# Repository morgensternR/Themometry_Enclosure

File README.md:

# Themometry_Enclosure
Initial Motherboard design to organize thermometry

 Copyright 2023 Ryan Morgenstern

   Licensed under the Apache License, Version 2.0 (the "License");
   you may not use this file except in compliance with the License.
   You may obtain a copy of the License at

       http://www.apache.org/licenses/LICENSE-2.0

   Unless required by applicable law or agreed to in writing, software
   distributed under the License is distributed on an "AS IS" BASIS,
   WITHOUT WARRANTIES OR CONDITIONS OF ANY KIND, either express or implied.
   See the License for the specific language governing permissions and
   limitations under the License.

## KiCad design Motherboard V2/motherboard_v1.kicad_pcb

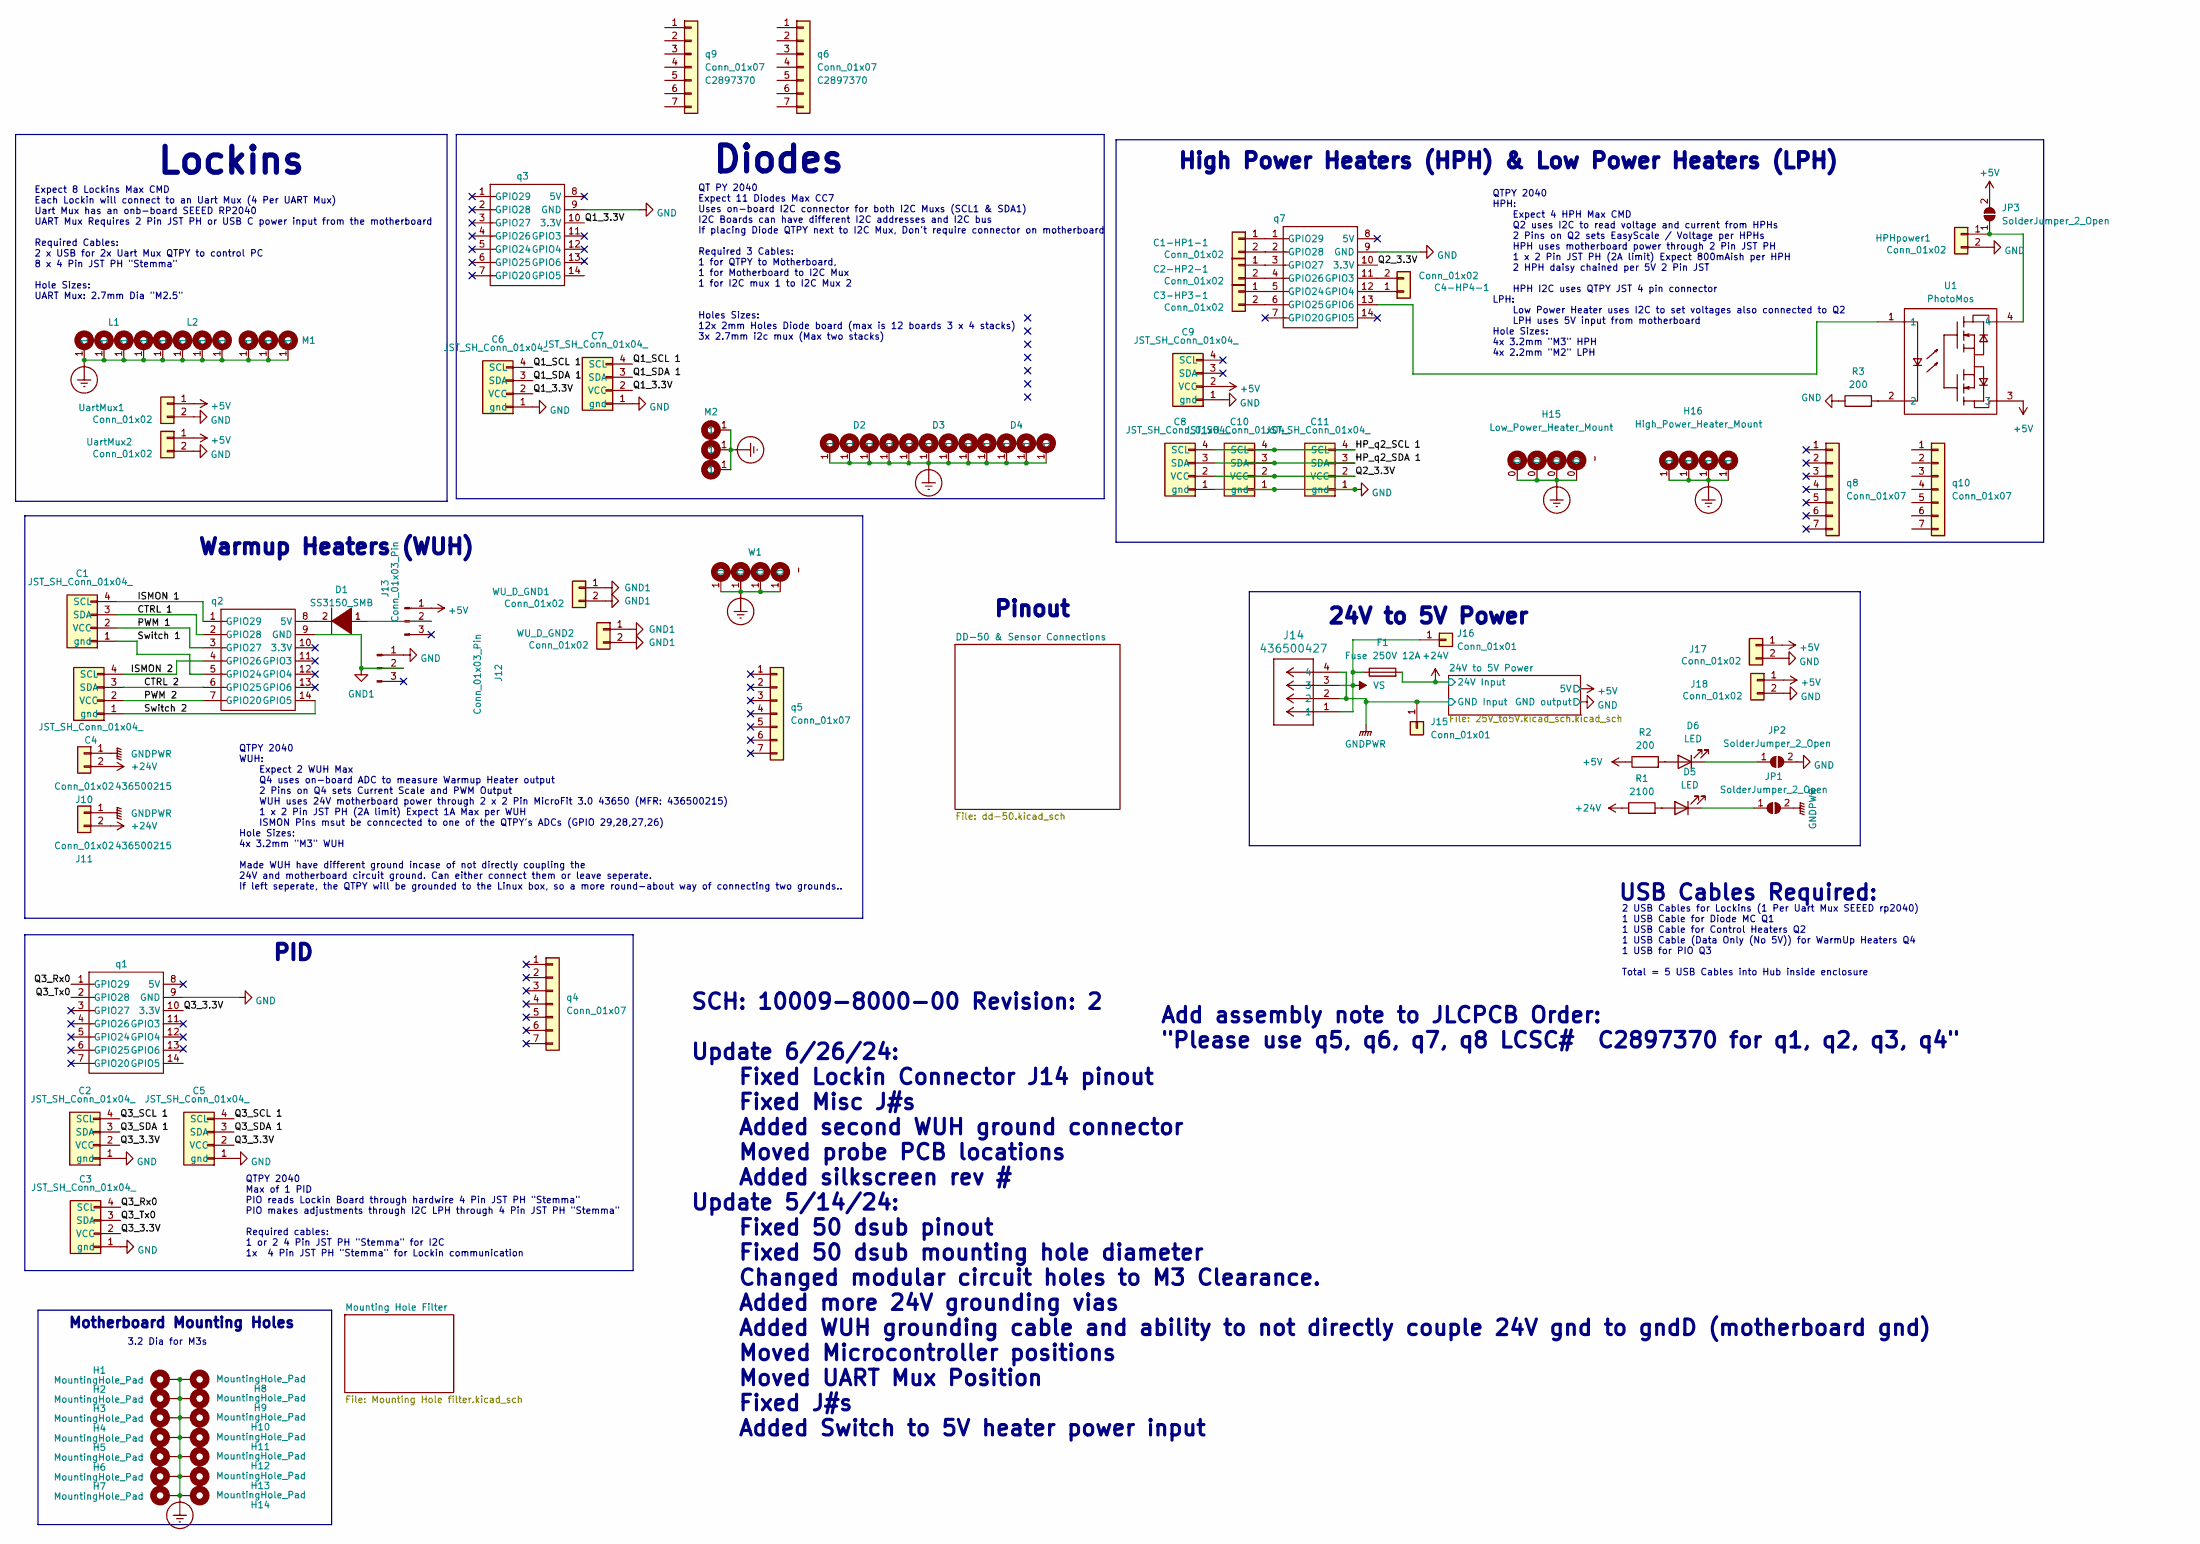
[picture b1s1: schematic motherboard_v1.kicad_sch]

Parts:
C1, C2, C3, C4, C5, C6, C7, C8, C9, C10, C11: JST_SH_Conn_01x04_; JST_SH_BM04B-SRSS-TB_1x04-1MP_P1.00mm_Vertical; MPN A1001WR-S; LCSC C160390
C1-HP1-1, C2-HP2-1, C3-HP3-1, C4-HP4-1: Conn_01x02; JST_PH_B2B-PH-K_1x02_P2.00mm_Vertical; LCSC C2683610
D1: SS3150_SMB; SMB_L4.6-W3.6-LS5.3-RD; LCSC C47124
D2, D3, D4: Diode_Board
D5, D6: LED; LED_0603_1608Metric_Pad1.05x0.95mm_HandSolder; LCSC C965804
F1: Fuse 250V 12A; Fuse_holder; LCSC C268204
H1, H2, H3, H4, H5, H6, H7, H8, H9, H10, H11, H12, H13, H14: MountingHole_Pad; Slot_Mounting_Hole
H15: Low_Power_Heater_Mount; Low_Power_Heater_Board
H16: High_Power_Heater_Mount; HPH_Board
HPHpower1: Conn_01x02; JST_PH_B2B-PH-K_1x02_P2.00mm_Vertical; LCSC C2683610
J10, J11: Conn_01x02; CONN-TH_436500215; LCSC C293740
J12, J13: Conn_01x03_Pin; PinHeader_1x03_P2.54mm_Vertical; LCSC C2937625
J14: 436500427; CON_436500427_MOL
J15: Conn_01x01; Test_Point_TH_BD3.2-D2.0; LCSC C5199811
J16: Conn_01x01; Test_Point_TH_BD3.2-D2.0; LCSC C5277086
J17, J18: Conn_01x02; JST_PH_B2B-PH-K_1x02_P2.00mm_Vertical; LCSC C2683610
JP1, JP2, JP3: SolderJumper_2_Open; SolderJumper-2_P1.3mm_Open_RoundedPad1.0x1.5mm
L1, L2: Lockin_board
M1: Uart Mux
M2: i2c_Mux
R1: 2100; R_0402_1005Metric; LCSC C2998067
R2, R3: 200; R_0402_1005Metric; LCSC C25087
U1: PhotoMos; HPH_Switch_SOP-4_L4.4-W4.3-P2.54-LS6.8-BL; LCSC C2691608
UartMux1, UartMux2: Conn_01x02; JST_PH_B2B-PH-K_1x02_P2.00mm_Vertical; LCSC C2683610
W1: Warmup circuit
WU_D_GND1, WU_D_GND2: Conn_01x02; JST_PH_B2B-PH-K_1x02_P2.00mm_Vertical; LCSC C2683610
q1, q2, q3, q7: Microcontroller-qtpy; LCSC C2897370
q4, q5, q6, q8, q9, q10: Conn_01x07; PinSocket_1x07_P2.54mm_Vertical; LCSC C2897370

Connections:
+5V: C9.2 (VCC), J13.1, J17.1, J18.1, JP3.2 (B), R2.1, U1.3, UartMux1.1, UartMux2.1; also elsewhere on the board
+24V: F1.2, J10.2, J11.2, R1.1; also elsewhere on the board
/CTRL 1: C1.3 (SDA), q2.2 (GPIO28)
/CTRL 2: C4.3 (SDA), q2.6 (GPIO25)
/HP_q2_SCL 1: C8.4 (SCL), C10.4 (SCL), C11.4 (SCL)
/HP_q2_SDA 1: C8.3 (SDA), C10.3 (SDA), C11.3 (SDA)
/ISMON 1: C1.4 (SCL), q2.1 (GPIO29)
/ISMON 2: C4.4 (SCL), q2.4 (GPIO26)
/PWM 1: C1.2 (VCC), q2.3 (GPIO27)
/PWM 2: C4.2 (VCC), q2.7 (GPIO20)
/Q1_3.3V: C6.2 (VCC), C7.2 (VCC), q3.10 (3.3V)
/Q1_SCL 1: C6.4 (SCL), C7.4 (SCL)
/Q1_SDA 1: C6.3 (SDA), C7.3 (SDA)
/Q2_3.3V: C8.2 (VCC), C10.2 (VCC), C11.2 (VCC), q7.10 (3.3V)
/Q3_3.3V: C2.2 (VCC), C3.2 (VCC), C5.2 (VCC), q1.10 (3.3V)
/Q3_Rx0: C3.4 (SCL), q1.1 (GPIO29)
/Q3_SCL 1: C2.4 (SCL), C5.4 (SCL)
/Q3_SDA 1: C2.3 (SDA), C5.3 (SDA)
/Q3_Tx0: C3.3 (SDA), q1.2 (GPIO28)
/Switch 1: C1.1 (gnd), q2.5 (GPIO24)
/Switch 2: C4.1 (gnd), q2.14 (GPIO5)
Earth_Protective: D2.1, D3.1, D4.1, H1.1, H2.1, H3.1, H4.1, H5.1, H6.1, H7.1, H8.1, H9.1, H10.1, H11.1, H12.1, H13.1, H14.1, H15.0, H16.1, L1.1, L2.1, M1.1, M2.1, W1.1 (0); also elsewhere on the board
GND: C2.1 (gnd), C3.1 (gnd), C5.1 (gnd), C6.1 (gnd), C7.1 (gnd), C8.1 (gnd), C9.1 (gnd), C10.1 (gnd), C11.1 (gnd), HPHpower1.2, J12.1, J17.2, J18.2, JP2.2 (B), R3.1, UartMux1.2, UartMux2.2, q1.9 (GND), q3.9 (GND), q7.9 (GND); also elsewhere on the board
GND1: J12.2, WU_D_GND1.1, WU_D_GND1.2, WU_D_GND2.1, WU_D_GND2.2, q2.9 (GND)
GNDPWR: J10.1, J11.1, J14.2, J14.4, J15.1, JP1.2 (B); also elsewhere on the board
unnamed: C1-HP1-1.1, q7.1 (GPIO29)
unnamed: C1-HP1-1.2, q7.2 (GPIO28)
unnamed: C2-HP2-1.1, q7.3 (GPIO27)
unnamed: C2-HP2-1.2, q7.4 (GPIO26)
unnamed: C3-HP3-1.1, q7.5 (GPIO24)
unnamed: C3-HP3-1.2, q7.6 (GPIO25)
unnamed: C4-HP4-1.1, q7.12 (GPIO4)
unnamed: C4-HP4-1.2, q7.11 (GPIO3)
unnamed: D1.2 (A), q2.8 (5V)
unnamed: D1.1 (K), J13.2
unnamed: D5.2 (A), R1.2
unnamed: D5.1 (K), JP1.1 (A)
unnamed: D6.2 (A), R2.2
unnamed: D6.1 (K), JP2.1 (A)
unnamed: HPHpower1.1, JP3.1 (A), U1.4
unnamed: R3.2, U1.2
unnamed: U1.1, q7.13 (GPIO6)
VS: F1.1, J14.1, J14.3, J16.1

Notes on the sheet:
High Power Heaters (HPH) & Low Power Heaters (LPH)
24V to 5V Power
QT PY 2040 Expect 11 Diodes Max CC7 Uses on-board I2C connector for both I2C Muxs (SCL1 & SDA1) I2C Boards can have different I2C addresses and I2C bus If placing Diode QTPY next to I2C Mux, Don't require connector on motherboard Required 3 Cables: 1 for QTPY to Motherboard, 1 for Motherboard to I2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
Diodes
Lockins
Expect 8 Lockins Max CMD Each Lockin will connect to an Uart Mux (4 Per UART Mux) Uart Mux has an onb-board SEEED RP2040 UART Mux Requires 2 Pin JST PH or USB C power input from the motherboard Required Cables: 2 x USB for 2x Uart Mux QTPY to control PC 8 x 4 Pin JST PH "Stemma" Hole Sizes: UART Mu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
Warmup Heaters (WUH)
QTPY 2040 HPH: Expect 4 HPH Max CMD Q2 uses I2C to read voltage and current from HPHs 2 Pins on Q2 sets EasyScale / Voltage per HPHs HPH uses motherboard power through 2 Pin JST PH 1 x 2 Pin JST PH (2A limit) Expect 800mAish per HPH 2 HPH daisy chained per 5V 2 Pin JST HPH I2C uses QTPY JST 4 pin c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
Pinout
PID
QTPY 2040 Max of 1 PID PIO reads Lockin Board through hardwire 4 Pin JST PH "Stemma" PIO makes adjustments through I2C LPH through 4 Pin JST PH "Stemma" Required cables: 1 or 2 4 Pin JST PH "Stemma" for I2C 1x 4 Pin JST PH "Stemma" for Lockin communication
USB Cables Required:
Motherboard Mounting Holes
Add assembly note to JLCPCB Order: "Please use q5, q6, q7, q8 LCSC# C2897370 for q1, q2, q3, q4"
SCH: 10009-8000-00 Revision: 2 Update 6/26/24: Fixed Lockin Connector J14 pinout Fixed Misc J#s Added second WUH ground connector Moved probe PCB locations Added silkscreen rev # Update 5/14/24: Fixed 50 dsub pinout Fixed 50 dsub mounting hole diameter Changed modular circuit holes to M3 Clearance.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
QTPY 2040 WUH: Expect 2 WUH Max Q4 uses on-board ADC to measure Warmup Heater output 2 Pins on Q4 sets Current Scale and PWM Output WUH uses 24V motherboard power through 2 x 2 Pin MicroFit 3.0 43650 (MFR: 436500215) 1 x 2 Pin JST PH (2A limit) Expect 1A Max per WUH ISMON Pins msut be conncected to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
3.2 Dia for M3s
2 USB Cables for Lockins (1 Per Uart Mux SEEED rp2040) 1 USB Cable for Diode MC Q1 1 USB Cable for Control Heaters Q2 1 USB Cable (Data Only (No 5V)) for WarmUp Heaters Q4 1 USB for PIO Q3 Total = 5 USB Cables into Hub inside enclosure

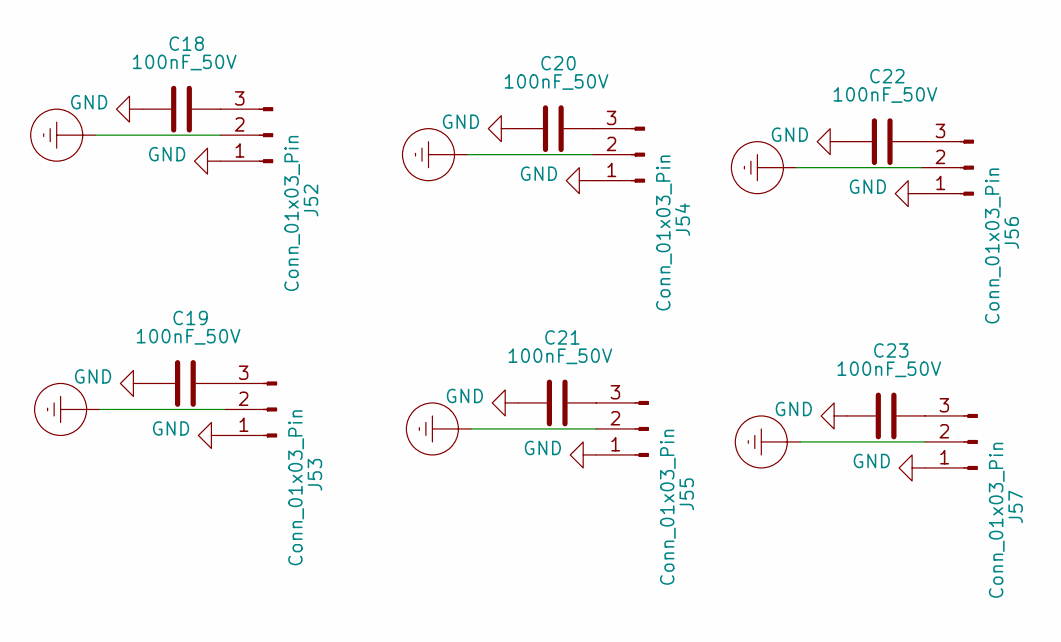
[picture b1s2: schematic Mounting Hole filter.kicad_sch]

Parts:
C18, C19, C20, C21, C22, C23: 100nF_50V; C_0402_1005Metric_Pad0.74x0.62mm_HandSolder; LCSC C307331
J52, J53, J54, J55, J56, J57: Conn_01x03_Pin; PinHeader_1x03_P2.54mm_Vertical; LCSC C2937625

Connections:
Earth_Protective: J52.2, J53.2, J54.2, J55.2, J56.2, J57.2; also elsewhere on the board
GND: C18.1, C19.1, C20.1, C21.1, C22.1, C23.1, J52.1, J53.1, J54.1, J55.1, J56.1, J57.1; also elsewhere on the board
unnamed: C18.2, J52.3
unnamed: C19.2, J53.3
unnamed: C20.2, J54.3
unnamed: C21.2, J55.3
unnamed: C22.2, J56.3
unnamed: C23.2, J57.3

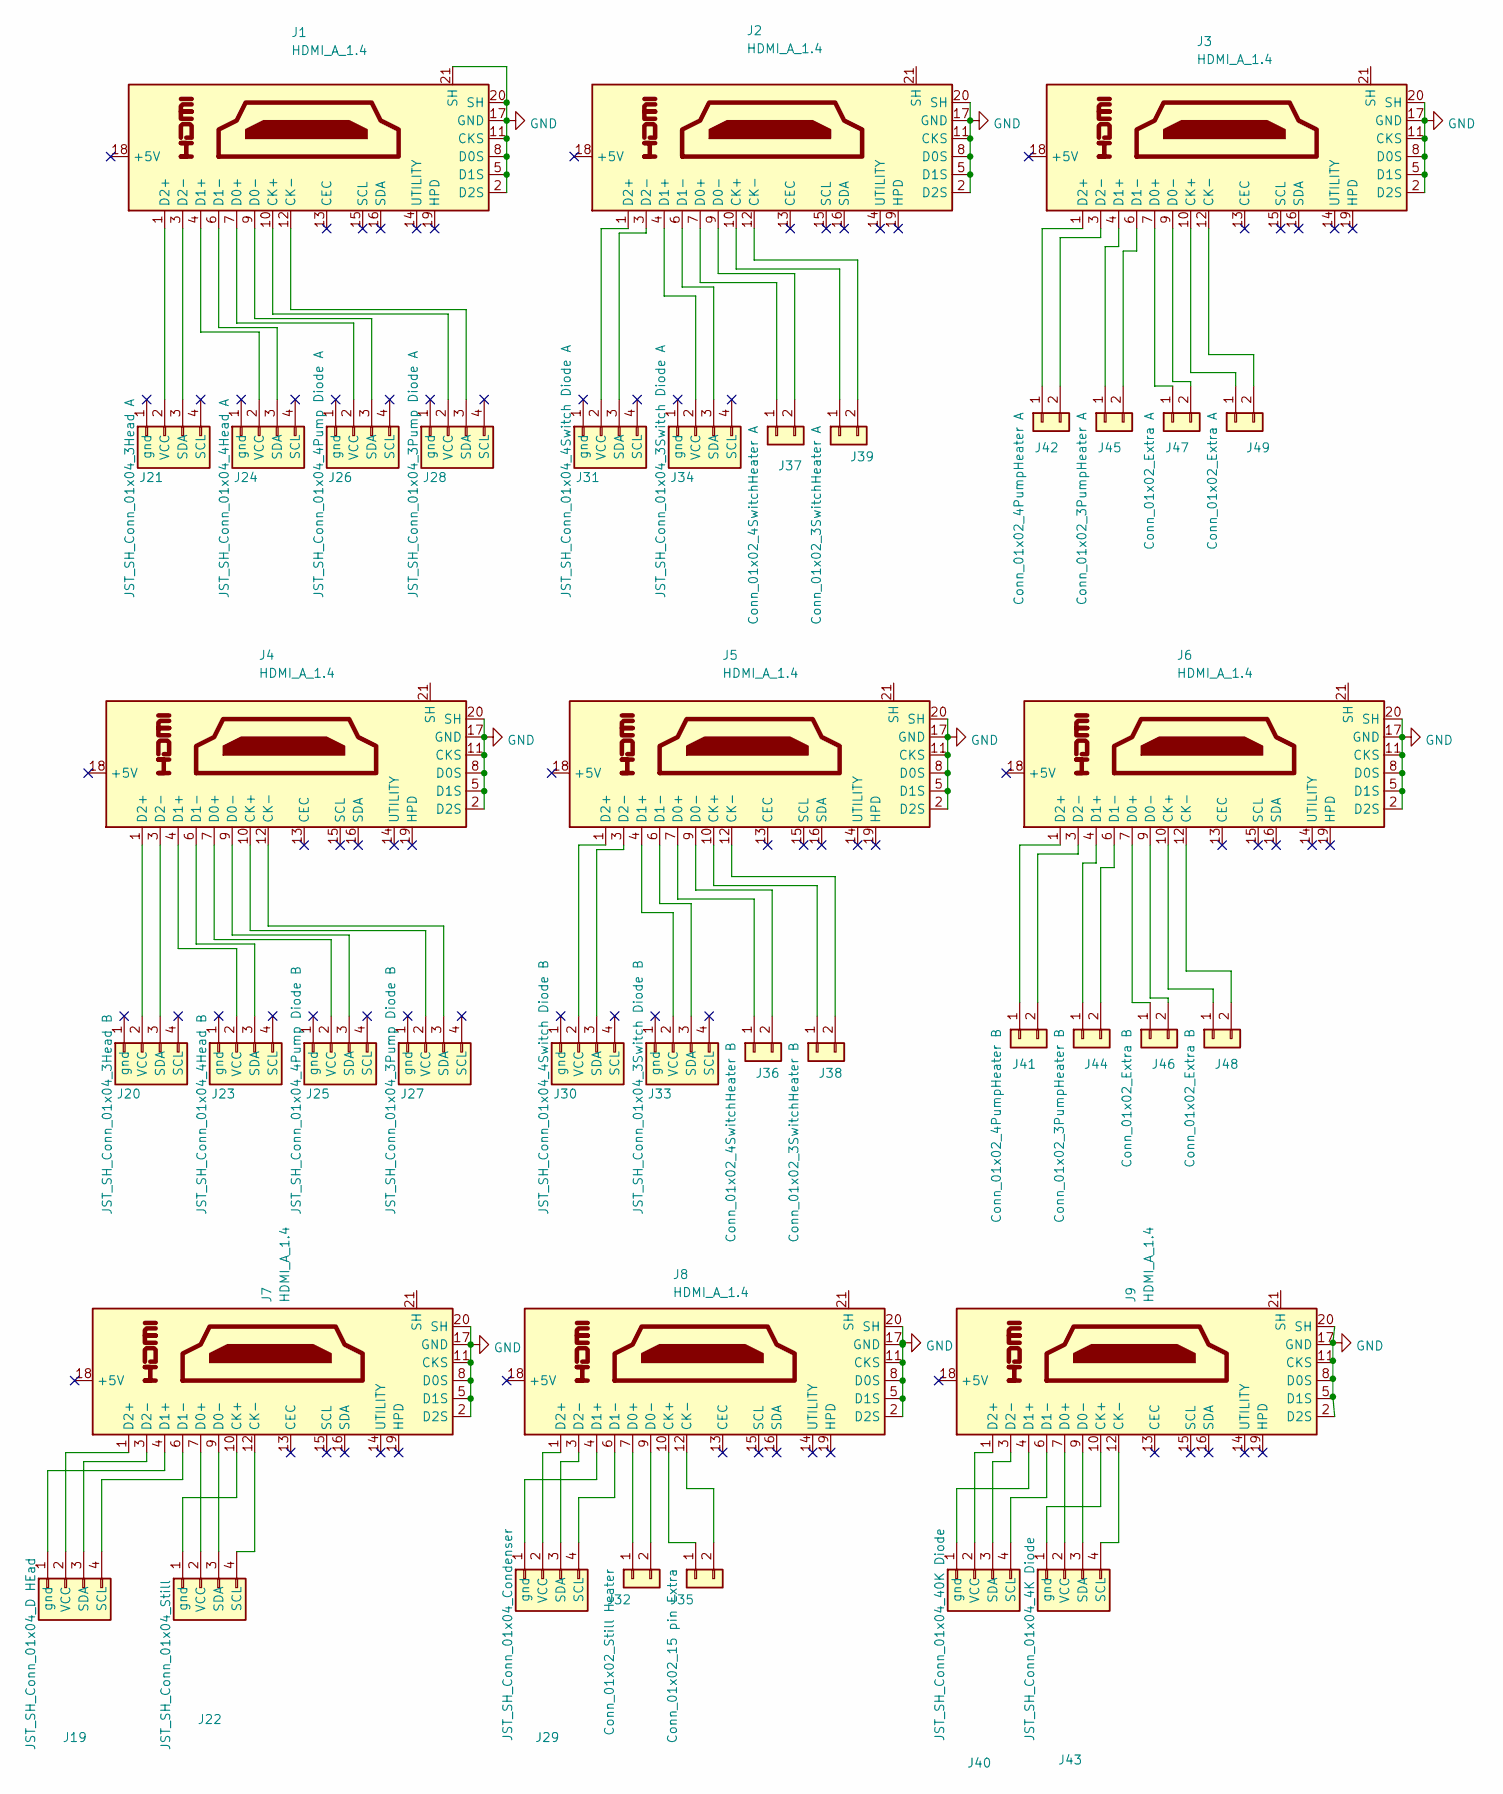
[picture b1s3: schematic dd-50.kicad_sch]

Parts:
J1, J2, J3, J4, J5, J6, J7, J8, J9: HDMI_A_1.4; HDMI-TH_D-HDMIM19P-FC00; LCSC C3025483
J19: JST_SH_Conn_01x04_D HEad; JST_SH_BM04B-SRSS-TB_1x04-1MP_P1.00mm_Vertical; MPN A1001WR-S; LCSC C160390
J20: JST_SH_Conn_01x04_3Head B; JST_SH_BM04B-SRSS-TB_1x04-1MP_P1.00mm_Vertical; MPN A1001WR-S; LCSC C160390
J21: JST_SH_Conn_01x04_3Head A; JST_SH_BM04B-SRSS-TB_1x04-1MP_P1.00mm_Vertical; MPN A1001WR-S; LCSC C160390
J22: JST_SH_Conn_01x04_Still; JST_SH_BM04B-SRSS-TB_1x04-1MP_P1.00mm_Vertical; MPN A1001WR-S; LCSC C160390
J23: JST_SH_Conn_01x04_4Head B; JST_SH_BM04B-SRSS-TB_1x04-1MP_P1.00mm_Vertical; MPN A1001WR-S; LCSC C160390
J24: JST_SH_Conn_01x04_4Head A; JST_SH_BM04B-SRSS-TB_1x04-1MP_P1.00mm_Vertical; MPN A1001WR-S; LCSC C160390
J25: JST_SH_Conn_01x04_4Pump Diode B; JST_SH_BM04B-SRSS-TB_1x04-1MP_P1.00mm_Vertical; MPN A1001WR-S; LCSC C160390
J26: JST_SH_Conn_01x04_4Pump Diode A; JST_SH_BM04B-SRSS-TB_1x04-1MP_P1.00mm_Vertical; MPN A1001WR-S; LCSC C160390
J27: JST_SH_Conn_01x04_3Pump Diode B; JST_SH_BM04B-SRSS-TB_1x04-1MP_P1.00mm_Vertical; MPN A1001WR-S; LCSC C160390
J28: JST_SH_Conn_01x04_3Pump Diode A; JST_SH_BM04B-SRSS-TB_1x04-1MP_P1.00mm_Vertical; MPN A1001WR-S; LCSC C160390
J29: JST_SH_Conn_01x04_Condenser; JST_SH_BM04B-SRSS-TB_1x04-1MP_P1.00mm_Vertical; MPN A1001WR-S; LCSC C160390
J30: JST_SH_Conn_01x04_4Switch Diode B; JST_SH_BM04B-SRSS-TB_1x04-1MP_P1.00mm_Vertical; MPN A1001WR-S; LCSC C160390
J31: JST_SH_Conn_01x04_4Switch Diode A; JST_SH_BM04B-SRSS-TB_1x04-1MP_P1.00mm_Vertical; MPN A1001WR-S; LCSC C160390
J32: Conn_01x02_Still Heater; JST_PH_B2B-PH-K_1x02_P2.00mm_Vertical; LCSC C5175230
J33: JST_SH_Conn_01x04_3Switch Diode B; JST_SH_BM04B-SRSS-TB_1x04-1MP_P1.00mm_Vertical; MPN A1001WR-S; LCSC C160390
J34: JST_SH_Conn_01x04_3Switch Diode A; JST_SH_BM04B-SRSS-TB_1x04-1MP_P1.00mm_Vertical; MPN A1001WR-S; LCSC C160390
J35: Conn_01x02_15 pin Extra; JST_PH_B2B-PH-K_1x02_P2.00mm_Vertical; LCSC C5175230
J36: Conn_01x02_4SwitchHeater B; JST_PH_B2B-PH-K_1x02_P2.00mm_Vertical; LCSC C5175230
J37: Conn_01x02_4SwitchHeater A; JST_PH_B2B-PH-K_1x02_P2.00mm_Vertical; LCSC C5175230
J38: Conn_01x02_3SwitchHeater B; JST_PH_B2B-PH-K_1x02_P2.00mm_Vertical; LCSC C5175230
J39: Conn_01x02_3SwitchHeater A; JST_PH_B2B-PH-K_1x02_P2.00mm_Vertical; LCSC C5175230
J40: JST_SH_Conn_01x04_40K Diode; JST_SH_BM04B-SRSS-TB_1x04-1MP_P1.00mm_Vertical; MPN A1001WR-S; LCSC C160390
J41: Conn_01x02_4PumpHeater B; JST_PH_B2B-PH-K_1x02_P2.00mm_Vertical; LCSC C5175230
J42: Conn_01x02_4PumpHeater A; JST_PH_B2B-PH-K_1x02_P2.00mm_Vertical; LCSC C5175230
J43: JST_SH_Conn_01x04_4K Diode; JST_SH_BM04B-SRSS-TB_1x04-1MP_P1.00mm_Vertical; MPN A1001WR-S; LCSC C160390
J44: Conn_01x02_3PumpHeater B; JST_PH_B2B-PH-K_1x02_P2.00mm_Vertical; LCSC C5175230
J45: Conn_01x02_3PumpHeater A; JST_PH_B2B-PH-K_1x02_P2.00mm_Vertical; LCSC C2683610
J46, J48: Conn_01x02_Extra B; JST_PH_B2B-PH-K_1x02_P2.00mm_Vertical; LCSC C5175230
J47, J49: Conn_01x02_Extra A; JST_PH_B2B-PH-K_1x02_P2.00mm_Vertical; LCSC C5175230

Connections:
GND: J1.2 (D2S), J1.5 (D1S), J1.8 (D0S), J1.11 (CKS), J1.17 (GND), J1.20 (SH), J1.21 (SH), J2.2 (D2S), J2.5 (D1S), J2.8 (D0S), J2.11 (CKS), J2.17 (GND), J2.20 (SH), J3.2 (D2S), J3.5 (D1S), J3.8 (D0S), J3.11 (CKS), J3.17 (GND), J3.20 (SH), J4.2 (D2S), J4.5 (D1S), J4.8 (D0S), J4.11 (CKS), J4.17 (GND), J4.20 (SH), J5.2 (D2S), J5.5 (D1S), J5.8 (D0S), J5.11 (CKS), J5.17 (GND), J5.20 (SH), J6.2 (D2S), J6.5 (D1S), J6.8 (D0S), J6.11 (CKS), J6.17 (GND), J6.20 (SH), J7.2 (D2S), J7.5 (D1S), J7.8 (D0S), J7.11 (CKS), J7.17 (GND), J7.20 (SH), J8.2 (D2S), J8.5 (D1S), J8.8 (D0S), J8.11 (CKS), J8.17 (GND), J8.20 (SH), J9.2 (D2S), J9.5 (D1S), J9.8 (D0S), J9.11 (CKS), J9.17 (GND), J9.20 (SH); also elsewhere on the board
unnamed: J1.10 (CK+), J28.2 (VCC)
unnamed: J1.12 (CK-), J28.3 (SDA)
unnamed: J1.7 (D0+), J26.2 (VCC)
unnamed: J1.9 (D0-), J26.3 (SDA)
unnamed: J1.4 (D1+), J24.2 (VCC)
unnamed: J1.6 (D1-), J24.3 (SDA)
unnamed: J1.1 (D2+), J21.2 (VCC)
unnamed: J1.3 (D2-), J21.3 (SDA)
unnamed: J2.10 (CK+), J39.1
unnamed: J2.12 (CK-), J39.2
unnamed: J2.7 (D0+), J37.1
unnamed: J2.9 (D0-), J37.2
unnamed: J2.4 (D1+), J34.2 (VCC)
unnamed: J2.6 (D1-), J34.3 (SDA)
unnamed: J2.1 (D2+), J31.2 (VCC)
unnamed: J2.3 (D2-), J31.3 (SDA)
unnamed: J3.10 (CK+), J49.1
unnamed: J3.12 (CK-), J49.2
unnamed: J3.7 (D0+), J47.1
unnamed: J3.9 (D0-), J47.2
unnamed: J3.4 (D1+), J45.1
unnamed: J3.6 (D1-), J45.2
unnamed: J3.1 (D2+), J42.1
unnamed: J3.3 (D2-), J42.2
unnamed: J7.6 (D1-), J19.4 (SCL)
unnamed: J7.3 (D2-), J19.3 (SDA)
unnamed: J7.1 (D2+), J19.2 (VCC)
unnamed: J7.4 (D1+), J19.1 (gnd)
unnamed: J4.3 (D2-), J20.3 (SDA)
unnamed: J4.1 (D2+), J20.2 (VCC)
unnamed: J7.12 (CK-), J22.4 (SCL)
unnamed: J7.9 (D0-), J22.3 (SDA)
unnamed: J7.7 (D0+), J22.2 (VCC)
unnamed: J7.10 (CK+), J22.1 (gnd)
unnamed: J4.6 (D1-), J23.3 (SDA)
unnamed: J4.4 (D1+), J23.2 (VCC)
unnamed: J4.9 (D0-), J25.3 (SDA)
unnamed: J4.7 (D0+), J25.2 (VCC)
unnamed: J4.12 (CK-), J27.3 (SDA)
unnamed: J4.10 (CK+), J27.2 (VCC)
unnamed: J8.6 (D1-), J29.4 (SCL)
unnamed: J8.3 (D2-), J29.3 (SDA)
unnamed: J8.1 (D2+), J29.2 (VCC)
unnamed: J8.4 (D1+), J29.1 (gnd)
unnamed: J5.3 (D2-), J30.3 (SDA)
unnamed: J5.1 (D2+), J30.2 (VCC)
unnamed: J8.7 (D0+), J32.1
unnamed: J8.9 (D0-), J32.2
unnamed: J5.6 (D1-), J33.3 (SDA)
unnamed: J5.4 (D1+), J33.2 (VCC)
unnamed: J8.10 (CK+), J35.1
unnamed: J8.12 (CK-), J35.2
unnamed: J5.7 (D0+), J36.1
unnamed: J5.9 (D0-), J36.2
unnamed: J5.10 (CK+), J38.1
unnamed: J5.12 (CK-), J38.2
unnamed: J9.6 (D1-), J40.4 (SCL)
unnamed: J9.3 (D2-), J40.3 (SDA)
unnamed: J9.1 (D2+), J40.2 (VCC)
unnamed: J9.4 (D1+), J40.1 (gnd)
unnamed: J6.1 (D2+), J41.1
unnamed: J6.3 (D2-), J41.2
unnamed: J9.12 (CK-), J43.4 (SCL)
unnamed: J9.9 (D0-), J43.3 (SDA)
unnamed: J9.7 (D0+), J43.2 (VCC)
unnamed: J9.10 (CK+), J43.1 (gnd)
unnamed: J6.4 (D1+), J44.1
unnamed: J6.6 (D1-), J44.2
unnamed: J6.7 (D0+), J46.1
unnamed: J6.9 (D0-), J46.2
unnamed: J6.10 (CK+), J48.1
unnamed: J6.12 (CK-), J48.2

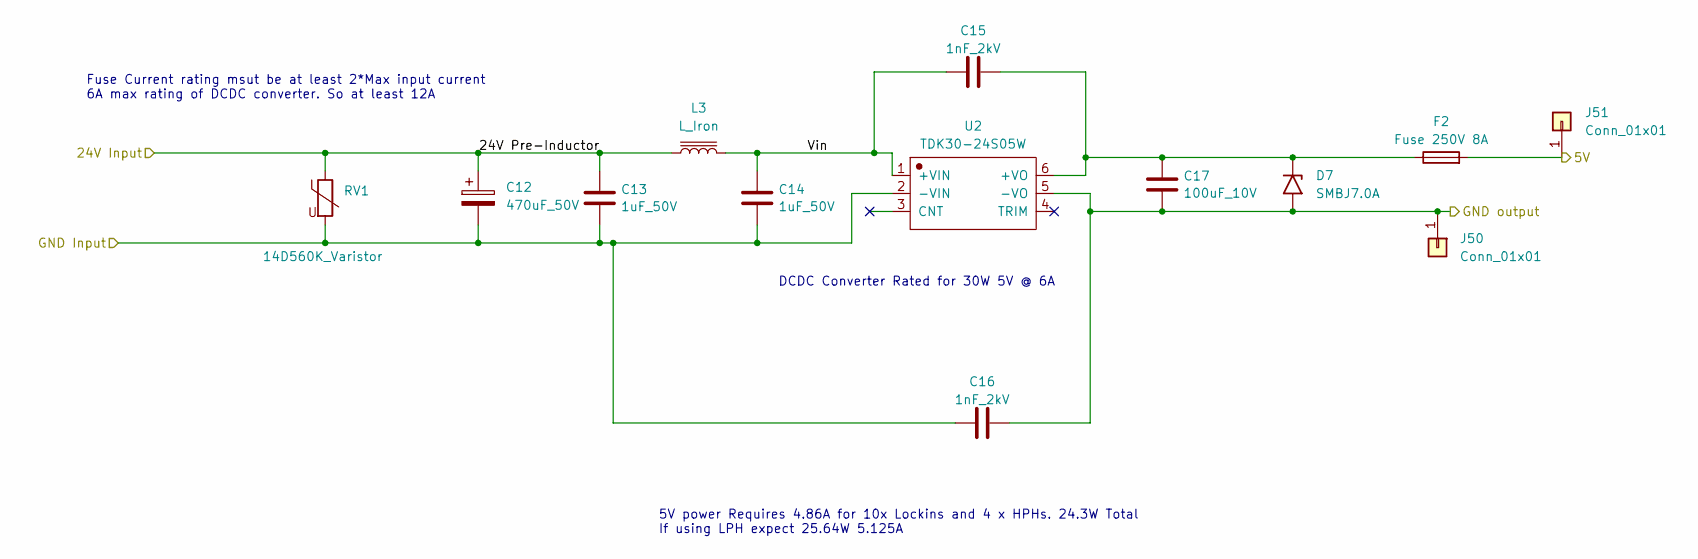
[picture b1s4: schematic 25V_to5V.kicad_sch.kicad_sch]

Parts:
C12: 470uF_50V; CP_Elec_10x10.5; LCSC C5162365
C13, C14: 1uF_50V; C_0603_1608Metric; LCSC C15849
C15, C16: 1nF_2kV; C_1206_3216Metric; LCSC C9196
C17: 100uF_10V; C_1206_3216Metric; LCSC C9196
D7: SMBJ7.0A; D_SMA; LCSC C693613
F2: Fuse 250V 8A; Fuse_holder; LCSC C268204
J50: Conn_01x01; Test_Point_TH_BD3.2-D2.0; LCSC C5199811
J51: Conn_01x01; Test_Point_TH_BD3.2-D2.0; LCSC C5277086
L3: L_Iron; IND-SMD_L7.1-W6.6; LCSC C439009
RV1: 14D560K_Varistor; RES-TH_L17.0-W5.0-P7.50-D1.2; LCSC C18901
U2: TDK30-24S05W; PWRM-TH_TDK30-XXSXX; LCSC C570789

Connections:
+5V: F2.2, J51.1; also elsewhere on the board
+24V: C12.1, C13.1, L3.1, RV1.1; also elsewhere on the board
/24V to 5V Power/Vin: C14.1, C15.1, L3.2, U2.1 (+VIN)
GND: C16.2, C17.2, D7.2 (A2), J50.1, U2.5 (-VO); also elsewhere on the board
GNDPWR: C12.2, C13.2, C14.2, C16.1, RV1.2, U2.2 (-VIN); also elsewhere on the board
unnamed: C15.2, C17.1, D7.1 (A1), F2.1, U2.6 (+VO)

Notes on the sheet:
DCDC Converter Rated for 30W 5V @ 6A
5V power Requires 4.86A for 10x Lockins and 4 x HPHs. 24.3W Total If using LPH expect 25.64W 5.125A
Fuse Current rating msut be at least 2*Max input current 6A max rating of DCDC converter. So at least 12A

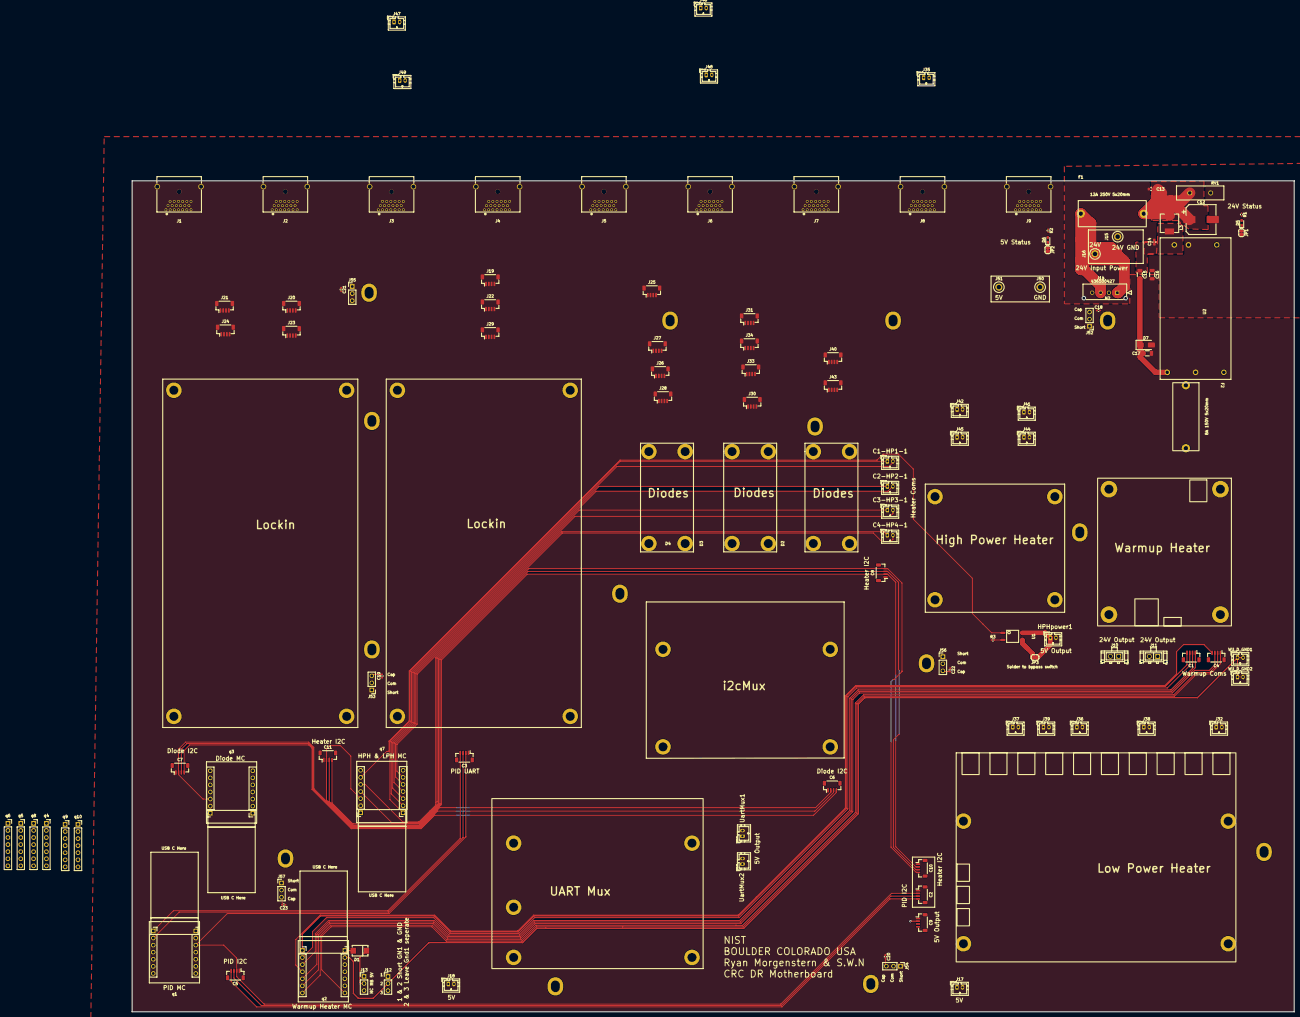
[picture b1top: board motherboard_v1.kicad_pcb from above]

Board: 6 copper layers, 417.0 x 298.1 mm, 139 parts (0 on the bottom side), 123 nets.

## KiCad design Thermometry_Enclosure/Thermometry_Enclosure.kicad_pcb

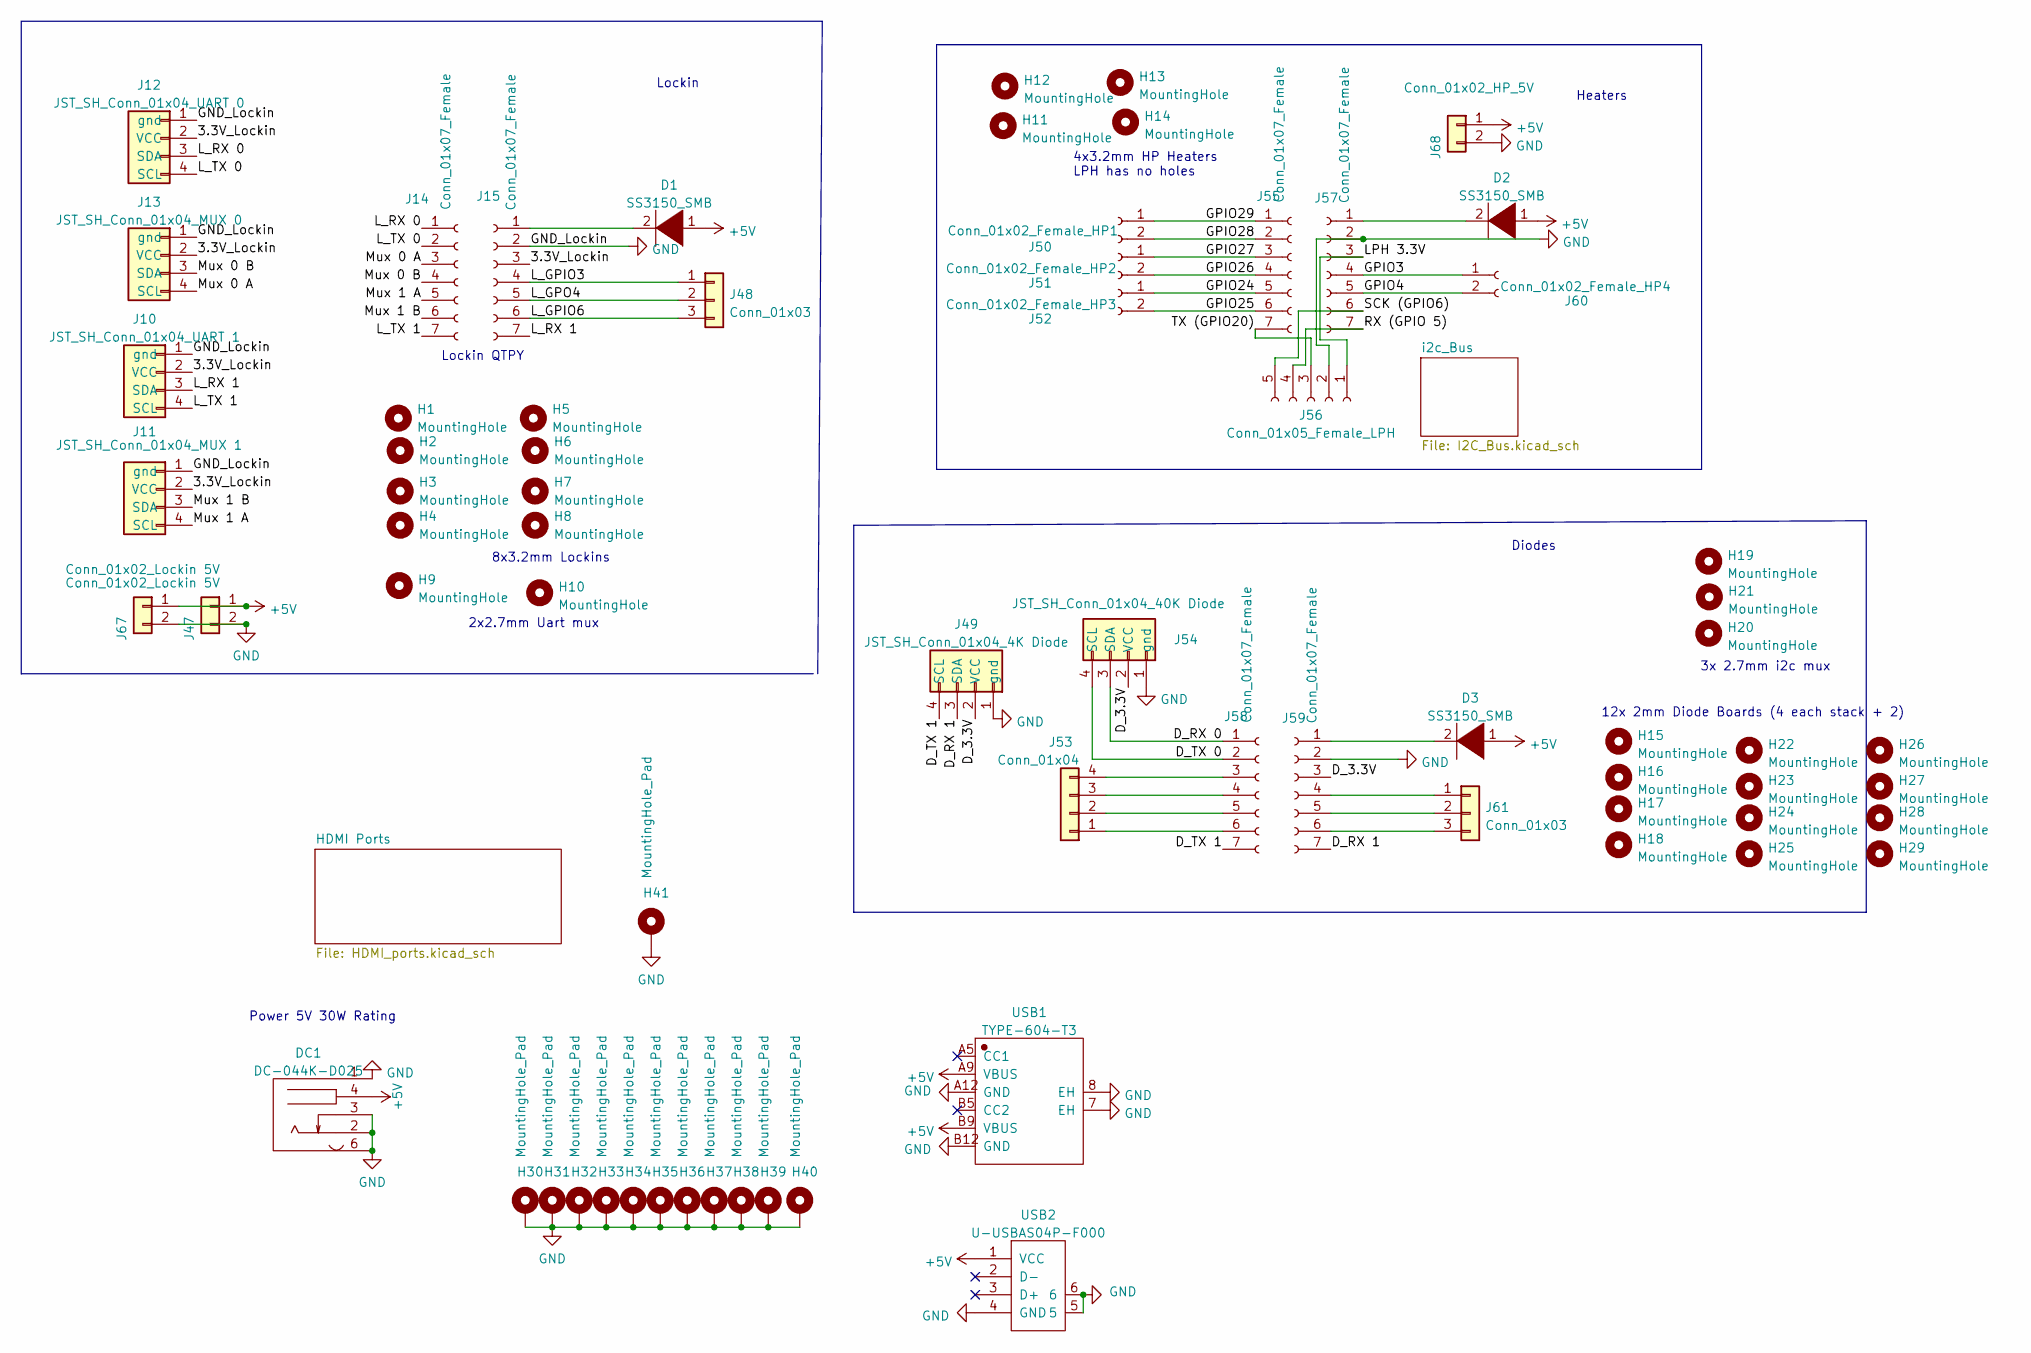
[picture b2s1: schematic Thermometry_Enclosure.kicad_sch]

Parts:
D1, D2, D3: SS3150_SMB; SMB_L4.6-W3.6-LS5.3-R-RD; LCSC C47124
DC1: DC-044K-D025; DC-IN-TH_DC-044K-D025; LCSC C963204
H1, H2, H3, H4, H5, H6, H7, H8, H11, H12, H13, H14: MountingHole; MountingHole_3.2mm_M3_Pad
H9, H10: MountingHole; MountingHole_2.7mm_Pad
H15, H16, H17, H18, H22, H23, H24, H25, H26, H27, H28, H29: MountingHole; MountingHole_2.2mm_M2_Pad
H19, H20, H21: MountingHole; MountingHole_2.7mm_M2.5_Pad
H30, H31, H32, H33, H34, H35, H36, H37, H38, H39, H40: MountingHole_Pad; MountingHole_5.3mm_M5_Pad
H41: MountingHole_Pad; MountingHole_6.5mm_Pad
J10: JST_SH_Conn_01x04_UART 1; JST_SH_BM04B-SRSS-TB_1x04-1MP_P1.00mm_Vertical; LCSC C160390
J11: JST_SH_Conn_01x04_MUX 1; JST_SH_BM04B-SRSS-TB_1x04-1MP_P1.00mm_Vertical; LCSC C160390
J12: JST_SH_Conn_01x04_UART 0; JST_SH_BM04B-SRSS-TB_1x04-1MP_P1.00mm_Vertical; LCSC C160390
J13: JST_SH_Conn_01x04_MUX 0; JST_SH_BM04B-SRSS-TB_1x04-1MP_P1.00mm_Vertical; LCSC C160390
J14, J15, J55, J57, J58, J59: Conn_01x07_Female; PinSocket_1x07_P2.54mm_Vertical; LCSC C2897370
J47, J67: Conn_01x02_Lockin 5V; JST_PH_B2B-PH-K_1x02_P2.00mm_Vertical; LCSC C2683610
J48, J61: Conn_01x03; PinSocket_1x03_P2.54mm_Vertical
J49: JST_SH_Conn_01x04_4K Diode; JST_SH_BM04B-SRSS-TB_1x04-1MP_P1.00mm_Vertical; LCSC C160390
J50: Conn_01x02_Female_HP1; PinSocket_1x02_P2.54mm_Vertical; LCSC C49661
J51: Conn_01x02_Female_HP2; PinSocket_1x02_P2.54mm_Vertical; LCSC C49661
J52: Conn_01x02_Female_HP3; PinSocket_1x02_P2.54mm_Vertical; LCSC C49661
J53: Conn_01x04; PinSocket_1x04_P2.54mm_Vertical
J54: JST_SH_Conn_01x04_40K Diode; JST_SH_BM04B-SRSS-TB_1x04-1MP_P1.00mm_Vertical; LCSC C160390
J56: Conn_01x05_Female_LPH; PinSocket_1x05_P2.54mm_Vertical; LCSC C50950
J60: Conn_01x02_Female_HP4; PinSocket_1x02_P2.54mm_Vertical; LCSC C49661
J68: Conn_01x02_HP_5V; JST_PH_B2B-PH-K_1x02_P2.00mm_Vertical; LCSC C2683610
USB1: TYPE-604-T3; USB-C-TH_TYPE-604-T3; LCSC C2689839
USB2: U-USBAS04P-F000; USB-A-TH_U-A-24DD-Y-2

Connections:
+5V: D1.1 (K), D2.1 (K), D3.1 (K), DC1.4, J47.1, J67.1, J68.1, USB1.A9 (VBUS), USB1.B9 (VBUS), USB2.1 (VCC)
/3.3V_Lockin: J10.2 (VCC), J11.2 (VCC), J12.2 (VCC), J13.2 (VCC), J15.3
/D_3.3V: J49.2 (VCC), J54.2 (VCC), J59.3
/D_RX 0: J54.3 (SDA), J58.1
/D_RX 1: J49.3 (SDA), J59.7
/D_TX 0: J54.4 (SCL), J58.2
/D_TX 1: J49.4 (SCL), J58.7
/GPIO3: J57.4, J60.1
/GPIO4: J57.5, J60.2
/GPIO24: J52.1, J55.5
/GPIO25: J52.2, J55.6
/GPIO26: J51.2, J55.4
/GPIO27: J51.1, J55.3
/GPIO28: J50.2, J55.2
/GPIO29: J50.1, J55.1
/LPH 3.3V: J56.1, J57.3
/L_GPIO3: J15.4, J48.1
/L_GPIO6: J15.6, J48.3
/L_GPO4: J15.5, J48.2
/L_RX 0: J12.3 (SDA), J14.1
/L_RX 1: J10.3 (SDA), J15.7
/L_TX 0: J12.4 (SCL), J14.2
/L_TX 1: J10.4 (SCL), J14.7
/Mux 0 A: J13.4 (SCL), J14.3
/Mux 0 B: J13.3 (SDA), J14.4
/Mux 1 A: J11.4 (SCL), J14.5
/Mux 1 B: J11.3 (SDA), J14.6
/RX (GPIO 5): J56.4, J57.7
/SCK (GPIO6): J56.5, J57.6
/TX (GPIO20): J55.7, J56.3
GND: DC1.1, DC1.2, DC1.3, DC1.6, H30.1, H31.1, H32.1, H33.1, H34.1, H35.1, H36.1, H37.1, H38.1, H39.1, H40.1, H41.1, J10.1 (gnd), J11.1 (gnd), J12.1 (gnd), J13.1 (gnd), J15.2, J47.2, J49.1 (gnd), J54.1 (gnd), J56.2, J57.2, J59.2, J67.2, J68.2, USB1.7 (EH), USB1.8 (EH), USB1.A12 (GND), USB1.B12 (GND), USB2.4 (GND), USB2.5, USB2.6; also elsewhere on the board
unnamed: D1.2 (A), J15.1
unnamed: D2.2 (A), J57.1
unnamed: D3.2 (A), J59.1
unnamed: J53.1, J58.6
unnamed: J53.2, J58.5
unnamed: J53.3, J58.4
unnamed: J53.4, J58.3
unnamed: J59.4, J61.1
unnamed: J59.5, J61.2
unnamed: J59.6, J61.3

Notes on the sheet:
12x 2mm Diode Boards (4 each stack + 2)
8x3.2mm Lockins
3x 2.7mm i2c mux
Lockin QTPY
Power 5V 30W Rating
2x2.7mm Uart mux
Heaters
Lockin
4x3.2mm HP Heaters LPH has no holes
Diodes
